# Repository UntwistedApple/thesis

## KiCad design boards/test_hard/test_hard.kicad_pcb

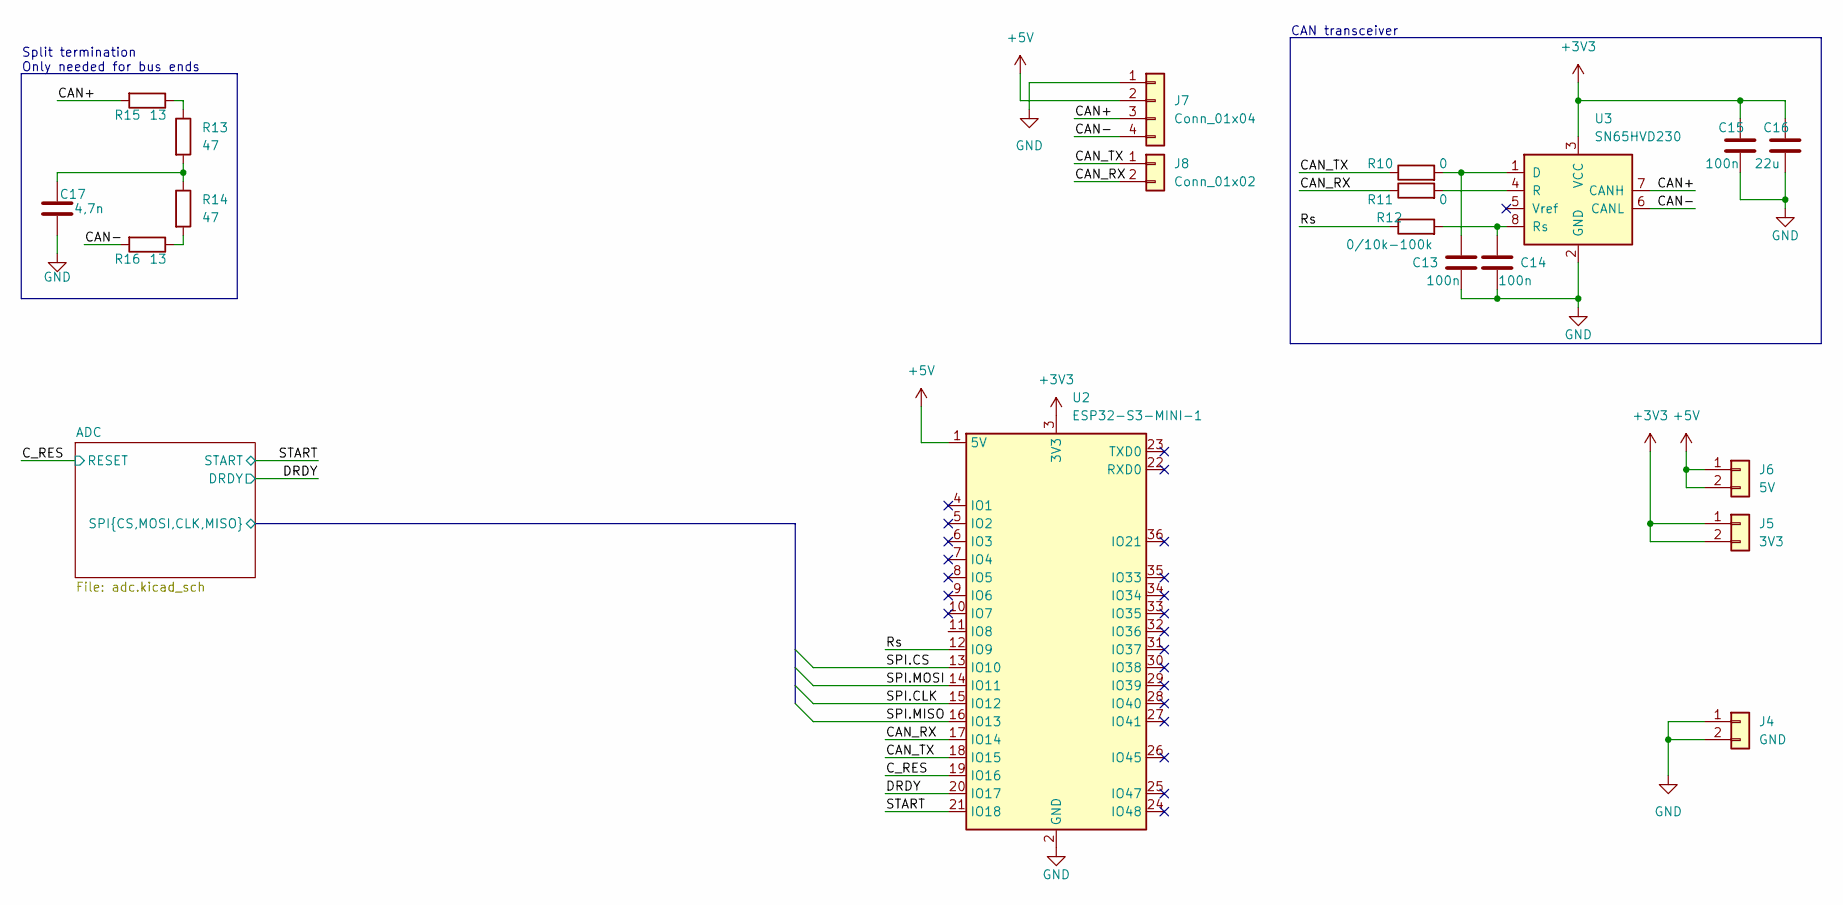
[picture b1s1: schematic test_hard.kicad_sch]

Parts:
C13, C14, C15: 100n; C_0603_1608Metric_Pad1.08x0.95mm_HandSolder
C16: 22u; C_0603_1608Metric_Pad1.08x0.95mm_HandSolder
C17: 4,7n; C_0603_1608Metric_Pad1.08x0.95mm_HandSolder
J4: GND; PinHeader_1x02_P2.54mm_Vertical
J5: 3V3; PinHeader_1x02_P2.54mm_Vertical
J6: 5V; PinHeader_1x02_P2.54mm_Vertical
J7: Conn_01x04; TerminalBlock_bornier-4_P5.08mm
J8: Conn_01x02; PinHeader_1x02_P2.54mm_Vertical
R10, R11: 0; R_0603_1608Metric_Pad0.98x0.95mm_HandSolder
R12: 0/10k-100k; R_0603_1608Metric_Pad0.98x0.95mm_HandSolder
R13, R14: 47; R_0603_1608Metric_Pad0.98x0.95mm_HandSolder
R15, R16: 13; R_0603_1608Metric_Pad0.98x0.95mm_HandSolder
U2: ESP32-S3-MINI-1; ESP32-S3-tiny
U3: SN65HVD230; SOIC-8_3.9x4.9mm_P1.27mm

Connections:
+3V3: C15.1, C16.1, J5.1, J5.2, U2.3 (3V3), U3.3 (VCC); also elsewhere on the board
+5V: J6.1, J6.2, J7.2, U2.1 (5V); also elsewhere on the board
/ADC/SPI.CLK: U2.15 (IO12); also elsewhere on the board
/ADC/SPI.CS: U2.13 (IO10); also elsewhere on the board
/ADC/SPI.MISO: U2.16 (IO13); also elsewhere on the board
/ADC/SPI.MOSI: U2.14 (IO11); also elsewhere on the board
/CAN+: J7.3, R15.2, U3.7 (CANH)
/CAN-: J7.4, R16.2, U3.6 (CANL)
/CAN_RX: J8.2, R11.1, U2.17 (IO14)
/CAN_TX: J8.1, R10.1, U2.18 (IO15)
/C_RES: U2.19 (IO16); also elsewhere on the board
/DRDY: U2.20 (IO17); also elsewhere on the board
/Rs: R12.1, U2.12 (IO9)
/START: U2.21 (IO18); also elsewhere on the board
GND: C13.2, C14.2, C15.2, C16.2, C17.2, J4.1, J4.2, J7.1, U2.2 (GND), U2.42 (GND), U2.43 (GND), U2.46 (GND), U2.47 (GND), U2.48 (GND), U2.49 (GND), U2.50 (GND), U2.51 (GND), U2.52 (GND), U2.53 (GND), U2.54 (GND), U2.55 (GND), U2.56 (GND), U2.57 (GND), U2.58 (GND), U2.59 (GND), U2.60 (GND), U2.61 (GND), U2.62 (GND), U2.63 (GND), U2.64 (GND), U2.65 (GND), U3.2 (GND); also elsewhere on the board
unnamed: C17.1, R13.2, R14.1
unnamed: R13.1, R15.1
unnamed: R14.2, R16.1
unnamed: C13.1, R10.2, U3.1 (D)
unnamed: R11.2, U3.4 (R)
unnamed: C14.1, R12.2, U3.8 (Rs)

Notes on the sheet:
Split termination Only needed for bus ends
CAN transceiver

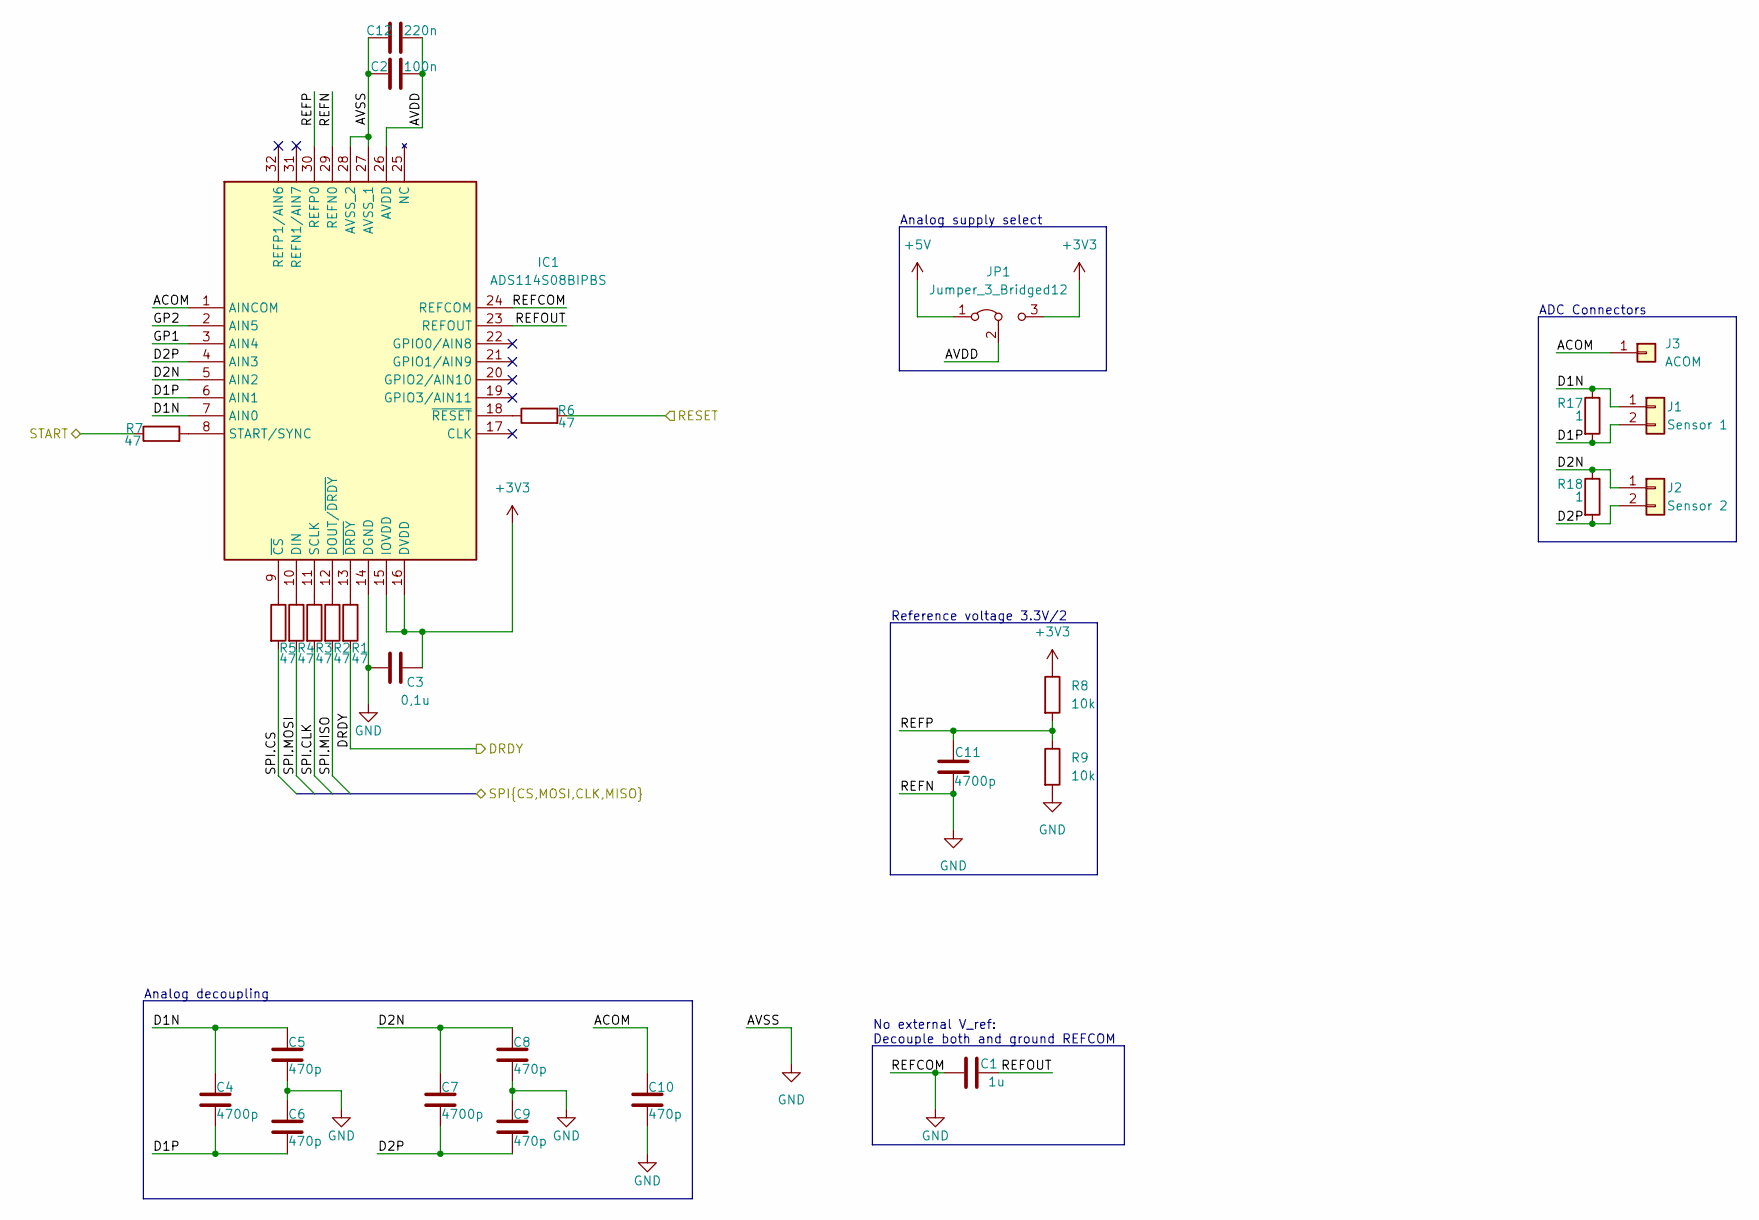
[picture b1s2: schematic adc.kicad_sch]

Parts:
C1: 1u; C_0603_1608Metric_Pad1.08x0.95mm_HandSolder
C2: 100n; C_0603_1608Metric_Pad1.08x0.95mm_HandSolder
C3: 0,1u; C_0603_1608Metric_Pad1.08x0.95mm_HandSolder
C4, C7, C11: 4700p; C_0603_1608Metric_Pad1.08x0.95mm_HandSolder
C5, C6, C8, C9, C10: 470p; C_0603_1608Metric_Pad1.08x0.95mm_HandSolder
C12: 220n; C_0603_1608Metric_Pad1.08x0.95mm_HandSolder
IC1: ADS114S08BIPBS; QFP50P700X700X120-32N; Mouser Part Number 595-ADS114S08BIPBS
J1: Sensor 1; SolderWire-0.1sqmm_1x02_P3.6mm_D0.4mm_OD1mm
J2: Sensor 2; SolderWire-0.1sqmm_1x02_P3.6mm_D0.4mm_OD1mm
J3: ACOM; SolderWire-0.1sqmm_1x01_D0.4mm_OD1mm
JP1: Jumper_3_Bridged12; PinHeader_1x03_P2.54mm_Vertical
R1, R2, R3, R4, R5, R6, R7: 47; R_0603_1608Metric_Pad0.98x0.95mm_HandSolder
R8, R9: 10k; R_0603_1608Metric_Pad0.98x0.95mm_HandSolder
R17, R18: 1; R_0603_1608Metric_Pad0.98x0.95mm_HandSolder

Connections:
+3V3: C3.2, IC1.15 (IOVDD), IC1.16 (DVDD), JP1.3 (B), R8.1; also elsewhere on the board
+5V: JP1.1 (A); also elsewhere on the board
/ADC/ACOM: C10.1, IC1.1 (AINCOM), J3.1
/ADC/AVDD: C2.2, C12.2, IC1.26 (AVDD), JP1.2 (C)
/ADC/D1N: C4.1, C5.1, IC1.7 (AIN0), J1.1, R17.1
/ADC/D1P: C4.2, C6.2, IC1.6 (AIN1), J1.2, R17.2
/ADC/D2N: C7.1, C8.1, IC1.5 (AIN2), J2.1, R18.1
/ADC/D2P: C7.2, C9.2, IC1.4 (AIN3), J2.2, R18.2
/ADC/GP1: IC1.3 (AIN4)
/ADC/GP2: IC1.2 (AIN5)
/ADC/REFOUT: C1.1, IC1.23 (REFOUT)
/ADC/REFP: C11.2, IC1.30 (REFP0), R8.2, R9.1
/ADC/SPI.CLK: R3.2; also elsewhere on the board
/ADC/SPI.CS: R5.2; also elsewhere on the board
/ADC/SPI.MISO: R2.2; also elsewhere on the board
/ADC/SPI.MOSI: R4.2; also elsewhere on the board
/C_RES: R6.2; also elsewhere on the board
/DRDY: R1.2; also elsewhere on the board
/START: R7.1; also elsewhere on the board
GND: C1.2, C2.1, C3.1, C5.2, C6.1, C8.2, C9.1, C10.2, C11.1, C12.1, IC1.14 (DGND), IC1.24 (REFCOM), IC1.27 (AVSS_1), IC1.28 (AVSS_2), IC1.29 (REFN0), R9.2; also elsewhere on the board
unnamed: IC1.10 (DIN), R4.1
unnamed: IC1.12 (DOUT/~DRDY), R2.1
unnamed: IC1.11 (SCLK), R3.1
unnamed: IC1.8 (START/SYNC), R7.2
unnamed: IC1.9 (~CS), R5.1
unnamed: IC1.13 (~DRDY), R1.1
unnamed: IC1.18 (~RESET), R6.1

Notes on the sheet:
ADC Connectors
Analog decoupling
No external V_ref: Decouple both and ground REFCOM
Reference voltage 3.3V/2
Analog supply select

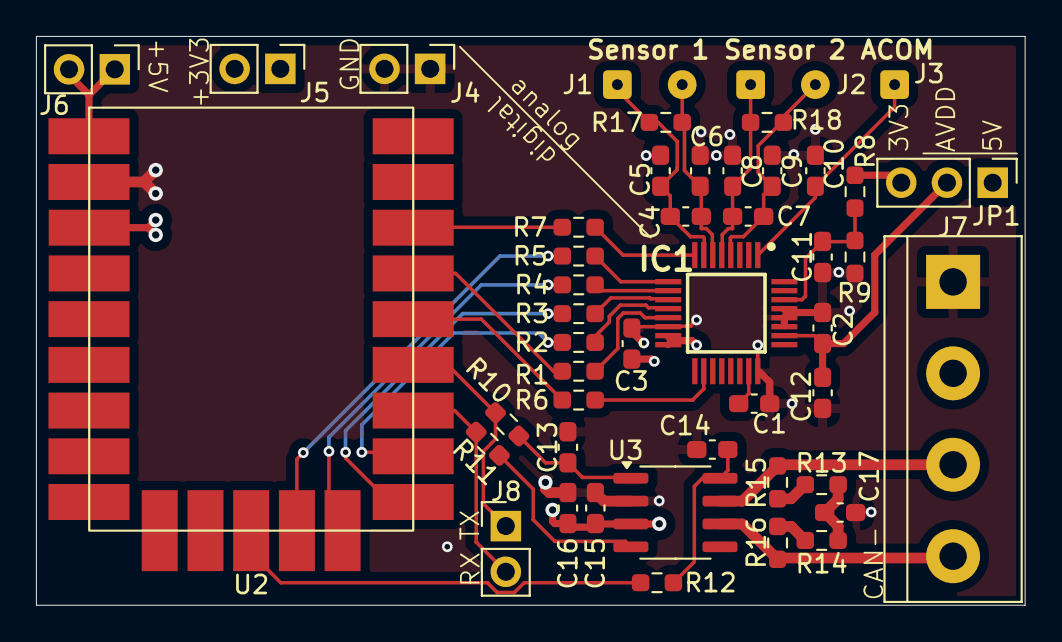
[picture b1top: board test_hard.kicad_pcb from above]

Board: 4 copper layers, 54.9 x 31.6 mm, 47 parts (0 on the bottom side), 36 nets.

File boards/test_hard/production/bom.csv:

Designator,Footprint,Quantity,Value,LCSC Part #
C1,0603,1,1u,
"C10, C5, C6, C8, C9",0603,5,470p,
"C11, C4, C7",0603,3,4700p,
C12,0603,1,220n,
"C13, C14, C15, C2",0603,4,100n,
C16,0603,1,22u,
C17,0603,1,"4,7n",
C3,0603,1,"0,1u",
IC1,QFP50P700X700X120-32N,1,ADS114S08BIPBS,
J1,SolderWire-0.1sqmm_1x02_P3.6mm_D0.4mm_OD1mm,1,Sensor 1,
J2,SolderWire-0.1sqmm_1x02_P3.6mm_D0.4mm_OD1mm,1,Sensor 2,
J3,SolderWire-0.1sqmm_1x01_D0.4mm_OD1mm,1,ACOM,
J4,PinHeader_1x02_P2.54mm_Vertical,1,GND,
J5,PinHeader_1x02_P2.54mm_Vertical,1,3V3,
J6,PinHeader_1x02_P2.54mm_Vertical,1,5V,
J7,TerminalBlock_bornier-4_P5.08mm,1,Conn_01x04,
J8,PinHeader_1x02_P2.54mm_Vertical,1,Conn_01x02,
"R1, R13, R14, R2, R3, R4, R5, R6, R7",0603,9,47,
"R10, R11",0603,2,0,
R12,0603,1,0/10k-100k,
"R15, R16",0603,2,13,
"R17, R18",0603,2,1,
"R8, R9",0603,2,10k,
U2,ESP32-S3-tiny,1,ESP32-S3-MINI-1,
U3,SOIC-8_3.9x4.9mm_P1.27mm,1,SN65HVD230,

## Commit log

2025-03-16 init
2025-03-23 Test Hardware Board
    Still missing CAN
2025-03-23 Add CAN support to test hardware
2025-03-24 1Ohm res and stencil
2025-04-02 Fabricated
2025-05-04 Working test_hard firmware
2025-05-14 boards/sensor: Change to thicker sensor
    New sensor has longer leads, bigger pads, thicker traces and a larger sensing area (20x20mm instead of 10x10mm)
2025-06-17 More sensor work
2025-06-17 Test-hard recent work
2025-06-17 Document work, add graphics and update notebook
2025-08-28 Aktueller Stand
2025-09-30 Current state update
